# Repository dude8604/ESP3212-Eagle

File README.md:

# ESP3212-Eagle

This is an Eagle library for the ESP3212 module.  It's untested, but it's based on the diagram on Expressif's Taobao store.

https://world.taobao.com/item/537990378649.htm?spm=a312a.7700714.0.0.tUASv9

I had to improvise for the pad sizes, so please let me know if it should be changed, or any other feedback.

If you've tested this and it works (or doesn't work) please tell me so I can post an update.

I also made a breakout board for it.

**Eagle Symbol for ESP3212**

**Eagle Package for ESP3212**

**Breakout Board for ESP3212**

It's now available [for sale here](https://www.tindie.com/products/dude8604/esp3212-breakout-board-alpha/).  I have them and I can ship within a day or two.

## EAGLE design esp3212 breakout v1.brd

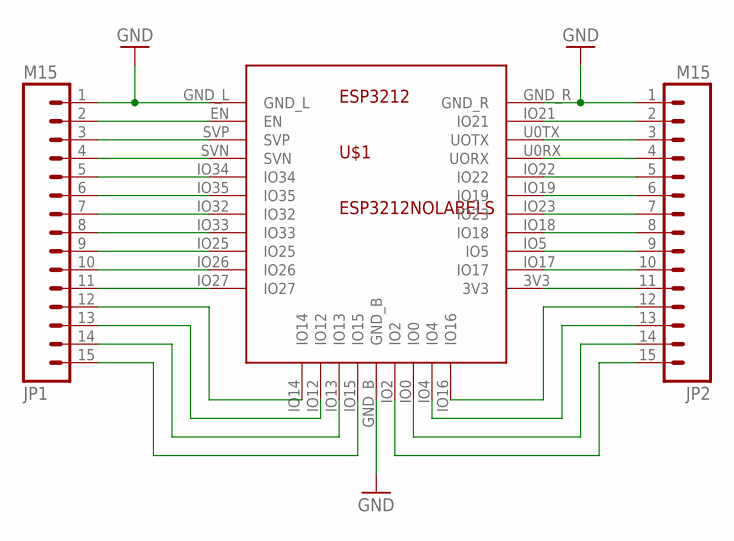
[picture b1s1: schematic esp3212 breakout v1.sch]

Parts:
JP1, JP2: M15; 1X15
U$1: ESP3212NOLABELS; ESP3212_NOPINLABELS

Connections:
GND: JP1.1, JP2.1, U$1.GND_B, U$1.GND_L, U$1.GND_R
unnamed: JP1.2, U$1.EN
unnamed: JP1.3, U$1.SVP
unnamed: JP1.4, U$1.SVN
unnamed: JP1.5, U$1.IO34
unnamed: JP1.6, U$1.IO35
unnamed: JP1.7, U$1.IO32
unnamed: JP1.8, U$1.IO33
unnamed: JP1.9, U$1.IO25
unnamed: JP1.10, U$1.IO26
unnamed: JP1.11, U$1.IO27
unnamed: JP2.2, U$1.IO21
unnamed: JP2.3, U$1.U0TX (UOTX)
unnamed: JP2.4, U$1.U0RX (UORX)
unnamed: JP2.5, U$1.IO22
unnamed: JP2.6, U$1.IO19
unnamed: JP2.7, U$1.IO23
unnamed: JP2.8, U$1.IO18
unnamed: JP2.9, U$1.IO5
unnamed: JP2.10, U$1.IO17
unnamed: JP2.11, U$1.3V3
unnamed: JP1.12, U$1.IO14
unnamed: JP1.13, U$1.IO12
unnamed: JP1.14, U$1.IO13
unnamed: JP1.15, U$1.IO15
unnamed: JP2.12, U$1.IO16
unnamed: JP2.13, U$1.IO4
unnamed: JP2.14, U$1.IO0
unnamed: JP2.15, U$1.IO2

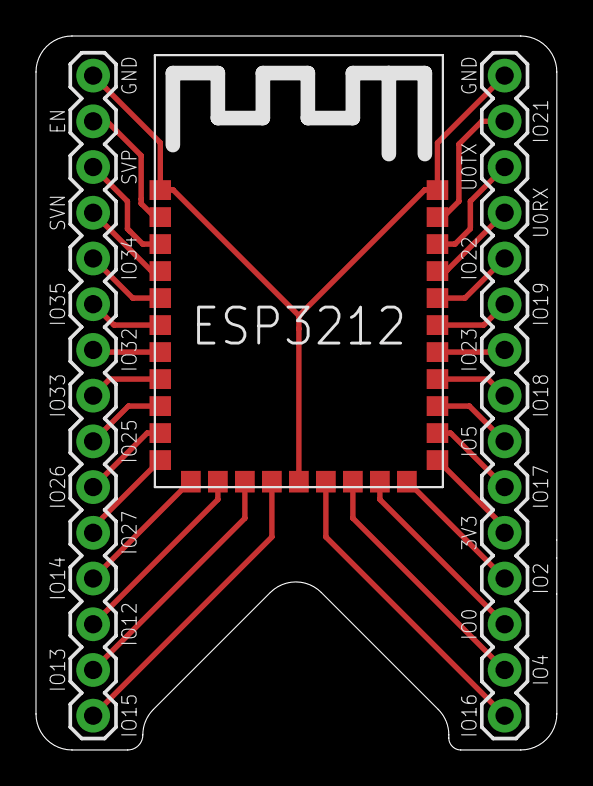
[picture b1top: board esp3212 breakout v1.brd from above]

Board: 2 copper layers, 28.9 x 39.7 mm, 3 parts (0 on the bottom side), 29 nets.

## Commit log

2016-09-08 Initial Commit
    Based on the image from Expressif's Taobao store for the ESP3212.
2016-09-08 added readme
2016-09-09 Added breakout board files
    If anyone tries it, let me know if it worked
2016-09-09 changed readme
2016-09-09 Added a version of the package without pin labels
    I used this one for the breakout
2016-09-09 Added preview images
2016-09-09 Fixed Image Filenames
2016-09-14 Added link to buy the breakout
2016-09-14 fixed links

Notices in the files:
parts and their libraries:
SparkFun-Connectors: Licensing: CC v3.0 Share-Alike You are welcome to use this library for commercial purposes.
